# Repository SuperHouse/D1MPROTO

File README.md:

Prototyping Shield for the WeMos D1 Mini
========================================

Copyright 2016 SuperHouse Automation Pty Ltd  
SuperHouse site:  www.superhouse.tv  
SuperHouse email: info@superhouse.tv  

A general purpose prototyping shield for the [WeMos D1 Mini][1], which is a microcontroller board based on the ESP8266 module.

Features:

 * Outline to match D1 Mini.
 * Headers with breakouts.
 * General purpose 0.1" grid for custom parts.

More information is available at:

  http://www.superhouse.tv/d1mproto

INSTALLATION
------------
The design is saved as an EAGLE project. EAGLE PCB design software is
available from www.cadsoftusa.com free for non-commercial use. To use
this project download it and place the directory containing these files
into the "eagle" directory on your computer.

DISTRIBUTION
------------
The specific terms of distribution of this project are governed by the
license referenced below.

LICENSE
-------
Licensed under the TAPR Open Hardware License (www.tapr.org/OHL).
The "license" folder within this repository also contains a copy of
this license in plain text format.

[1]: http://www.wemos.cc/wiki/doku.php?id=en:d1_mini

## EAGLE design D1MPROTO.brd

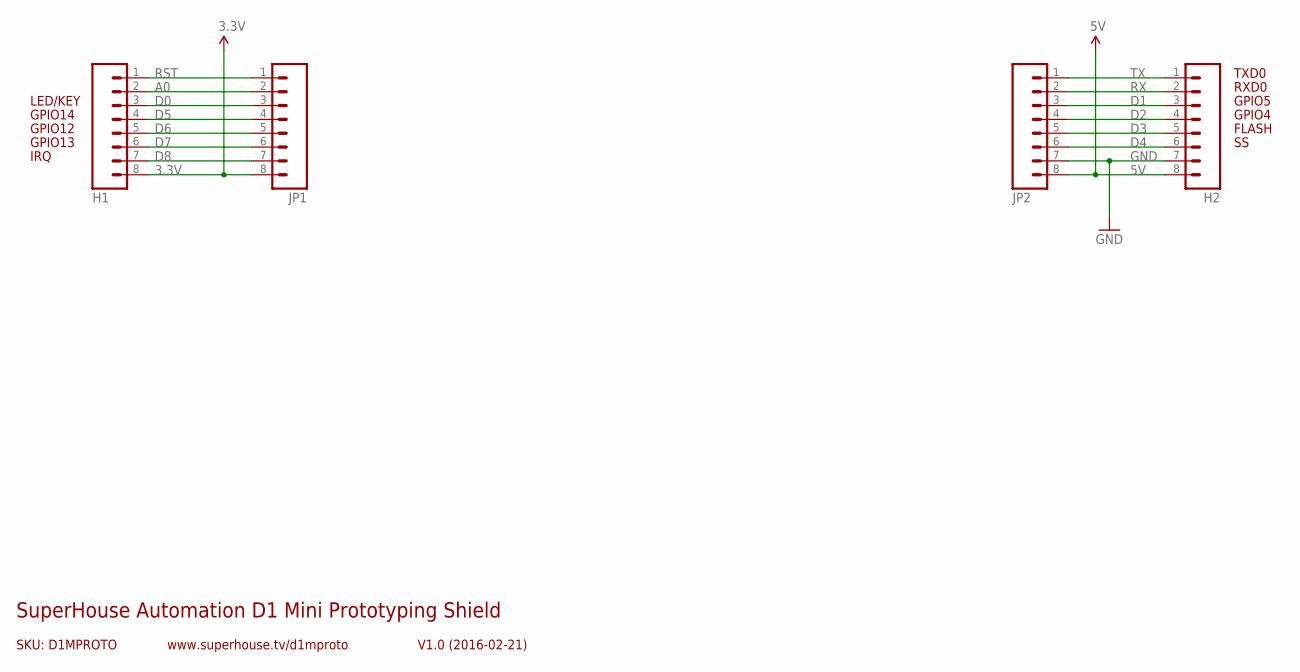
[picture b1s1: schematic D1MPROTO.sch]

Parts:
H1, H2: M08; 1X08
JP1, JP2: M08; 1X08

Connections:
3.3V: H1.8, JP1.8
5V: H2.8, JP2.8
A0: H1.2, JP1.2
D0: H1.3, JP1.3
D1: H2.3, JP2.3
D2: H2.4, JP2.4
D3: H2.5, JP2.5
D4: H2.6, JP2.6
D5: H1.4, JP1.4
D6: H1.5, JP1.5
D7: H1.6, JP1.6
D8: H1.7, JP1.7
GND: H2.7, JP2.7
RST: H1.1, JP1.1
RX: H2.2, JP2.2
TX: H2.1, JP2.1

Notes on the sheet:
FLASH
GPIO12
GPIO4
GPIO5
RXD0
TXD0
GPIO13
GPIO14
IRQ
LED/KEY
SKU: D1MPROTO
SuperHouse Automation D1 Mini Prototyping Shield
V1.0 (2016-02-21)
www.superhouse.tv/d1mproto

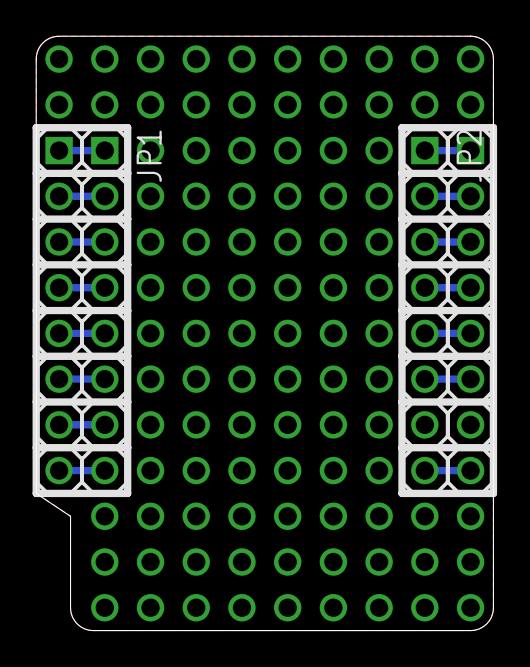
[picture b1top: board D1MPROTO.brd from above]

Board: 2 copper layers, 25.4 x 33.0 mm, 4 parts (0 on the bottom side), 16 nets.

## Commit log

2016-02-26 Initial import
2016-02-26 Added license and preview images, and updated README

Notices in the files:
parts and their libraries:
freetronics-original: Licensing: CC v3.0 Share-Alike You are welcome to use this library for commercial purposes.
